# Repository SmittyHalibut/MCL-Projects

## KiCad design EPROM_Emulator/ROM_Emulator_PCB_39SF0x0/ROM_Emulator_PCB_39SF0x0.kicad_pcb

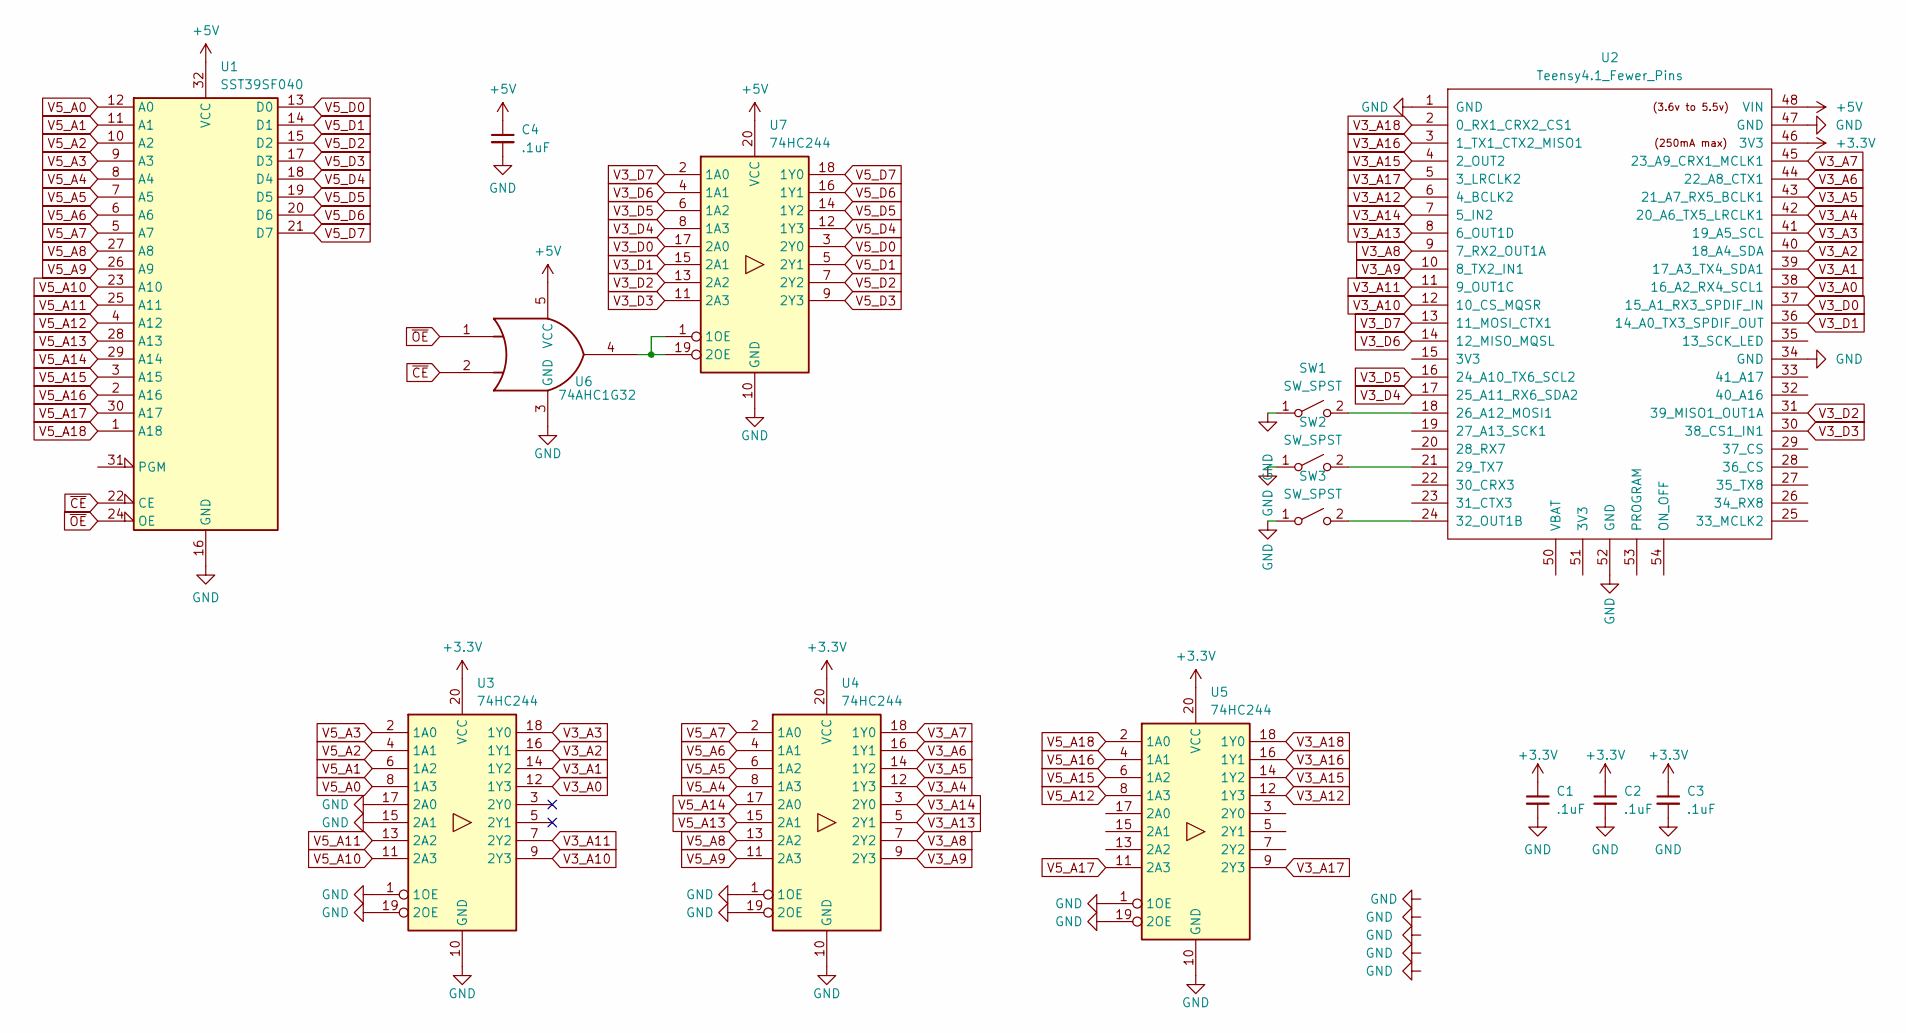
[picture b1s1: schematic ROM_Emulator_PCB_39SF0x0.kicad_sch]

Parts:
C1, C2, C3, C4: .1uF; C_0603_1608Metric; LCSC C15849
SW1, SW2, SW3: SW_SPST; SW_SPST_B3U-1000P-B; LCSC C498294
U1: SST39SF040; DIP-32_W15.24mm_Socket
U2: Teensy4.1_Fewer_Pins; Teensy41_Fewer_Pins
U3, U4, U5, U7: 74HC244; TSSOP-20_4.4x6.5mm_P0.65mm; LCSC C5623
U6: 74AHC1G32; SOT-353_SC-70-5; LCSC C12489

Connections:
+3.3V: C1.1, C2.1, C3.1, U2.46 (3V3), U3.20 (VCC), U4.20 (VCC), U5.20 (VCC)
+5V: C4.1, U1.32 (VCC), U2.48 (VIN), U6.5 (VCC), U7.20 (VCC)
GND: C1.2, C2.2, C3.2, C4.2, SW1.1 (A), SW2.1 (A), SW3.1 (A), U1.16 (GND), U2.1 (GND), U2.34 (GND), U2.47 (GND), U2.52 (GND), U3.1 (1OE), U3.10 (GND), U3.15 (2A1), U3.17 (2A0), U3.19 (2OE), U4.1 (1OE), U4.10 (GND), U4.19 (2OE), U5.1 (1OE), U5.10 (GND), U5.19 (2OE), U6.3 (GND), U7.10 (GND)
unnamed: SW1.2 (B), U2.18 (26_A12_MOSI1)
unnamed: SW2.2 (B), U2.21 (29_TX7)
unnamed: SW3.2 (B), U2.24 (32_OUT1B)
unnamed: U6.4, U7.1 (1OE), U7.19 (2OE)
V3_A0: U2.38 (16_A2_RX4_SCL1), U3.12 (1Y3)
V3_A1: U2.39 (17_A3_TX4_SDA1), U3.14 (1Y2)
V3_A2: U2.40 (18_A4_SDA), U3.16 (1Y1)
V3_A3: U2.41 (19_A5_SCL), U3.18 (1Y0)
V3_A4: U2.42 (20_A6_TX5_LRCLK1), U4.12 (1Y3)
V3_A5: U2.43 (21_A7_RX5_BCLK1), U4.14 (1Y2)
V3_A6: U2.44 (22_A8_CTX1), U4.16 (1Y1)
V3_A7: U2.45 (23_A9_CRX1_MCLK1), U4.18 (1Y0)
V3_A8: U2.9 (7_RX2_OUT1A), U4.7 (2Y2)
V3_A9: U2.10 (8_TX2_IN1), U4.9 (2Y3)
V3_A10: U2.12 (10_CS_MQSR), U3.9 (2Y3)
V3_A11: U2.11 (9_OUT1C), U3.7 (2Y2)
V3_A12: U2.6 (4_BCLK2), U5.12 (1Y3)
V3_A13: U2.8 (6_OUT1D), U4.5 (2Y1)
V3_A14: U2.7 (5_IN2), U4.3 (2Y0)
V3_A15: U2.4 (2_OUT2), U5.14 (1Y2)
V3_A16: U2.3 (1_TX1_CTX2_MISO1), U5.16 (1Y1)
V3_A17: U2.5 (3_LRCLK2), U5.9 (2Y3)
V3_A18: U2.2 (0_RX1_CRX2_CS1), U5.18 (1Y0)
V3_D0: U2.37 (15_A1_RX3_SPDIF_IN), U7.17 (2A0)
V3_D1: U2.36 (14_A0_TX3_SPDIF_OUT), U7.15 (2A1)
V3_D2: U2.31 (39_MISO1_OUT1A), U7.13 (2A2)
V3_D3: U2.30 (38_CS1_IN1), U7.11 (2A3)
V3_D4: U2.17 (25_A11_RX6_SDA2), U7.8 (1A3)
V3_D5: U2.16 (24_A10_TX6_SCL2), U7.6 (1A2)
V3_D6: U2.14 (12_MISO_MQSL), U7.4 (1A1)
V3_D7: U2.13 (11_MOSI_CTX1), U7.2 (1A0)
V5_A0: U1.12 (A0), U3.8 (1A3)
V5_A1: U1.11 (A1), U3.6 (1A2)
V5_A2: U1.10 (A2), U3.4 (1A1)
V5_A3: U1.9 (A3), U3.2 (1A0)
V5_A4: U1.8 (A4), U4.8 (1A3)
V5_A5: U1.7 (A5), U4.6 (1A2)
V5_A6: U1.6 (A6), U4.4 (1A1)
V5_A7: U1.5 (A7), U4.2 (1A0)
V5_A8: U1.27 (A8), U4.13 (2A2)
V5_A9: U1.26 (A9), U4.11 (2A3)
V5_A10: U1.23 (A10), U3.11 (2A3)
V5_A11: U1.25 (A11), U3.13 (2A2)
V5_A12: U1.4 (A12), U5.8 (1A3)
V5_A13: U1.28 (A13), U4.15 (2A1)
V5_A14: U1.29 (A14), U4.17 (2A0)
V5_A15: U1.3 (A15), U5.6 (1A2)
V5_A16: U1.2 (A16), U5.4 (1A1)
V5_A17: U1.30 (A17), U5.11 (2A3)
V5_A18: U1.1 (A18), U5.2 (1A0)
V5_D0: U1.13 (D0), U7.3 (2Y0)
V5_D1: U1.14 (D1), U7.5 (2Y1)
V5_D2: U1.15 (D2), U7.7 (2Y2)
V5_D3: U1.17 (D3), U7.9 (2Y3)
V5_D4: U1.18 (D4), U7.12 (1Y3)
V5_D5: U1.19 (D5), U7.14 (1Y2)
V5_D6: U1.20 (D6), U7.16 (1Y1)
V5_D7: U1.21 (D7), U7.18 (1Y0)
~CE: U1.22 (CE), U6.2
~OE: U1.24 (OE), U6.1

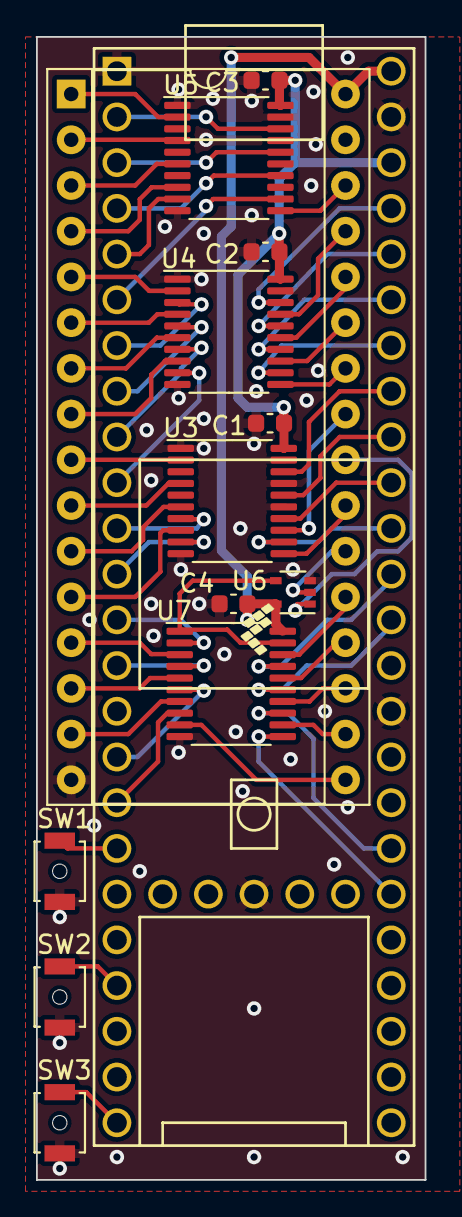
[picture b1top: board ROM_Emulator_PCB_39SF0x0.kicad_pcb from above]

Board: 2 copper layers, 21.6 x 63.5 mm, 14 parts (0 on the bottom side), 63 nets.

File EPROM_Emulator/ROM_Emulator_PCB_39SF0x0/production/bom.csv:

Designator,Footprint,Quantity,Value,LCSC Part #
"C1, C2, C3, C4",0603,4,.1uF,C15849
"SW1, SW2, SW3",SW_SPST_B3U-1000P-B,3,SW_SPST,C498294
"U3, U4, U5, U7",TSSOP-20_4.4x6.5mm_P0.65mm,4,74HC244,C5623
U6,SOT-353_SC-70-5,1,74AHC1G32,C12489

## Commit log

2023-07-09 Added a design for 39SF0x0, as used in RC2014 Micro+
2023-07-09 Bugfix: OR'd OE# and CE# together, used for both halves of data 244. Added some buttons. Freed up D13 for LED use.
2023-07-09 Made macros for bit manipulation, to ease changing pins around.
